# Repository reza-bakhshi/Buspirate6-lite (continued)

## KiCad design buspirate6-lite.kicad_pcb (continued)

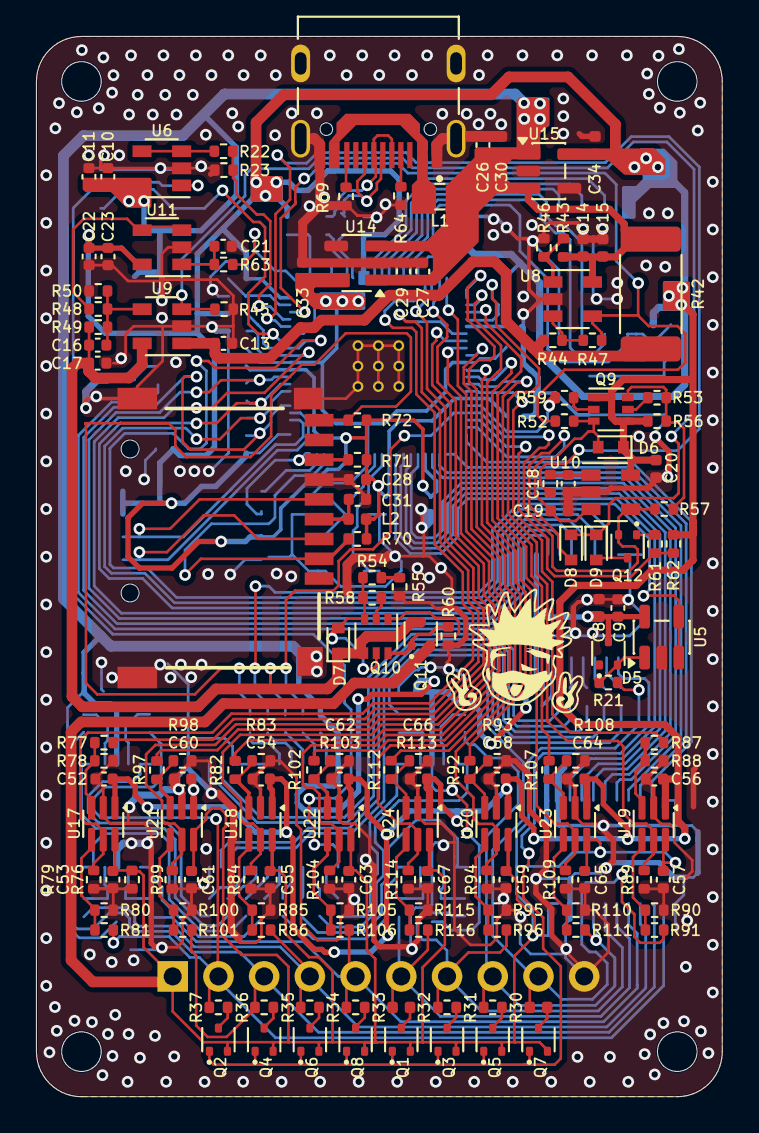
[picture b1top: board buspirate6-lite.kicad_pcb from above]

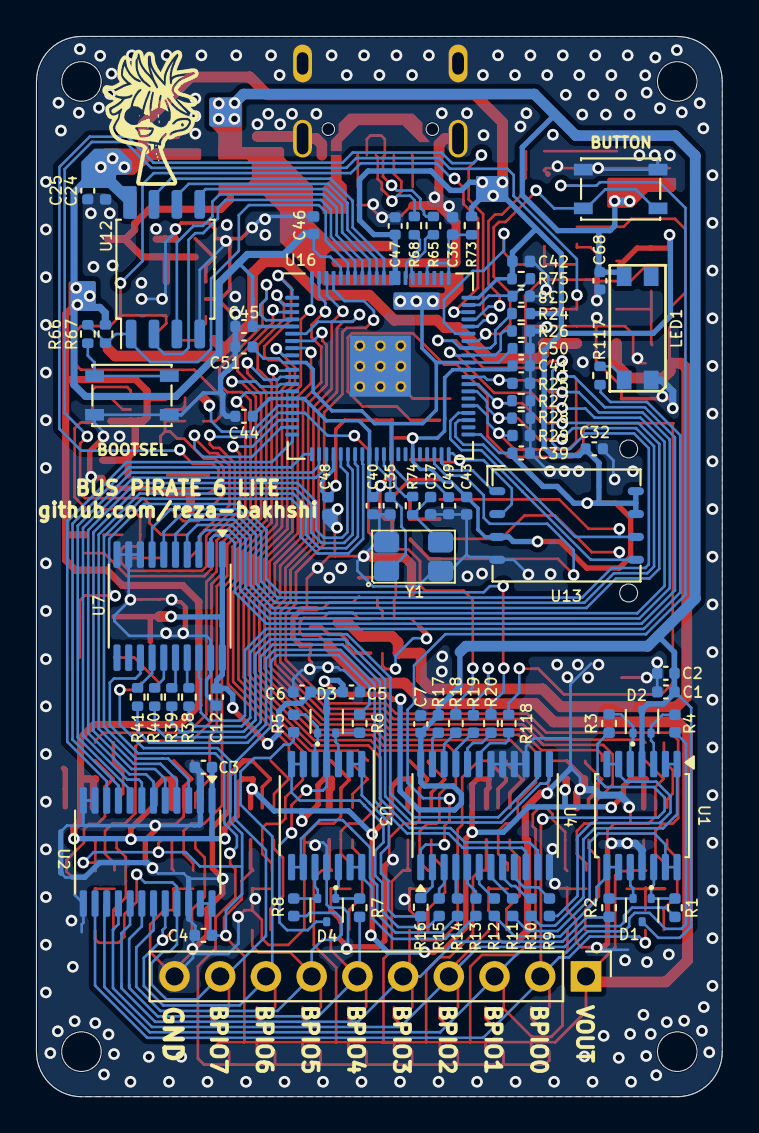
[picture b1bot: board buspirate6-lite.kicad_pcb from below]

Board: 2 copper layers, 38.1 x 58.9 mm, 244 parts (87 on the bottom side), 165 nets.

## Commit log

2026-04-14 buspirate6-lite [v1.0.0]
2026-04-14 buspirate6-lite [v1.0.0
2026-04-14 add readme file
2026-04-14 add readme.md file
